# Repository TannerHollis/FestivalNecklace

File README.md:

# FestivalNecklace
 Fun RGB ATTiny Festival Necklace

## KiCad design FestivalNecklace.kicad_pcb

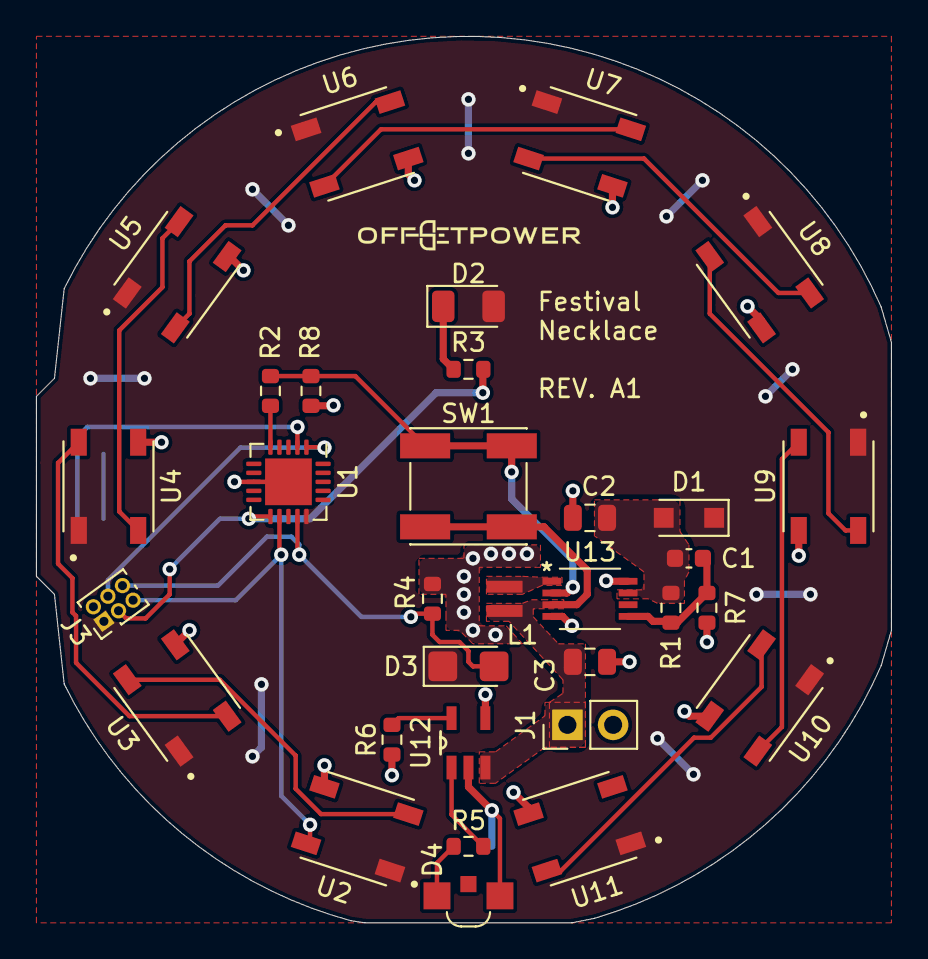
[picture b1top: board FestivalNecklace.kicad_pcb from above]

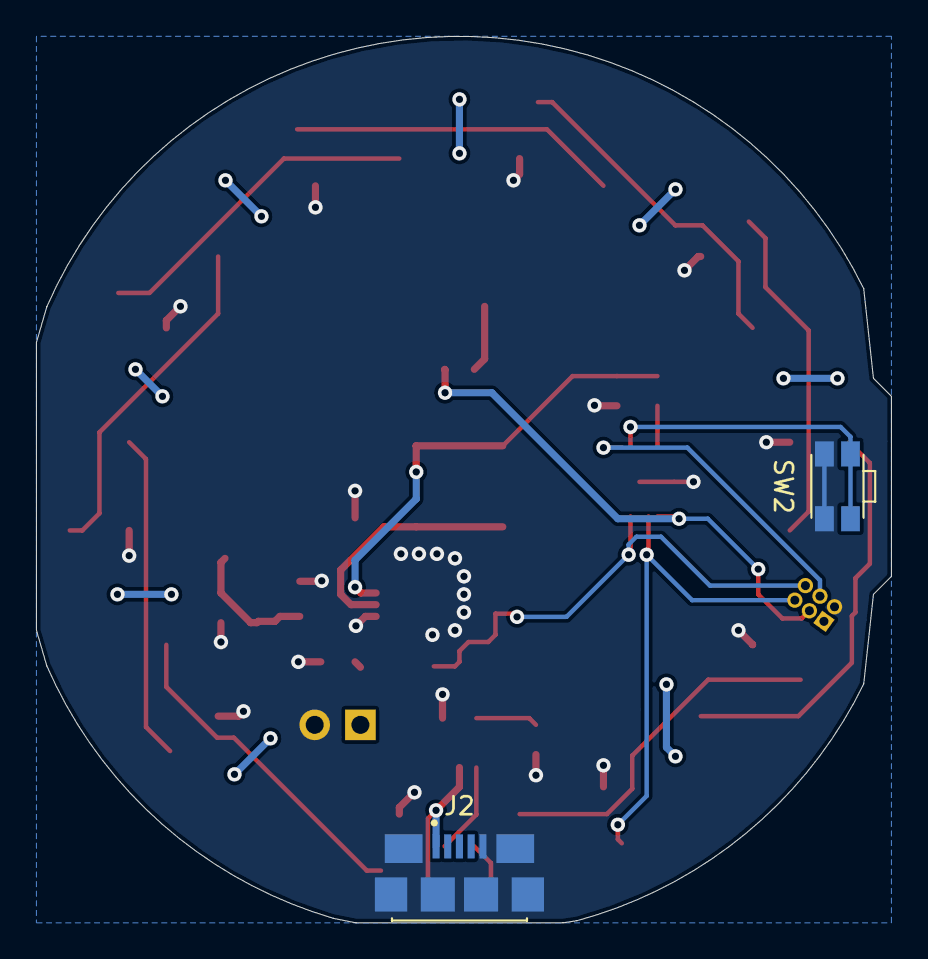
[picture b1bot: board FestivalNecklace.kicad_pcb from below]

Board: 2 copper layers, 47.5 x 49.2 mm, 34 parts (2 on the bottom side), 27 nets.

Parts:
C1: 1n; C_0603_1608Metric
C2: 22uF; C_0805_2012Metric
C3: 10uF; C_0805_2012Metric
D1: D_Schottky; D_SOD-123F
D2: LED; LED_1206_3216Metric
D3: D_Photo; LED_1206_3216Metric_Castellated
D4: LED; APA3010SECK
J1: Conn_01x02; PinHeader_1x02_P2.54mm_Vertical
J2: 10118192-0002LF; AMPHENOL_10118192-0002LF
J3: Conn_02x03_Odd_Even; PinHeader_2x03_P1.00mm_Vertical
L1: 2.2u; NRS2012T2R2MGJ
R1: 750k; R_0603_1608Metric
R2, R5: 1.5k; R_0603_1608Metric
R3: 50; R_0603_1608Metric
R4: 470k; R_0603_1608Metric
R6: 4.7k; R_0603_1608Metric
R7, R8: 100k; R_0603_1608Metric
SW1: SW_Push_Dual; TL3301NF260QG
SW2: SW_Push_Dual; EVQ-P7C01P
U1: ATtiny45V-10MU; QFN-20-1EP_4x4mm_P0.5mm_EP2.6x2.6mm
U2, U3, U4, U5, U6, U7, U8, U9, U10, U11: WS2812B-B; LED_WS2812B-B
U12: MCP73832T-2ACI_OT; SOT95P270X145-5N
U13: PAM2401SCADJ

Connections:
BTTN: SW2.2, U1.2
EN: R2.2, R8.2, SW1.1, U13.2
GND: C2.2, C3.2, J1.2, J2.5, J2.S1, J2.S2, J2.S3, J2.S4, J2.S5, J2.S6, J3.2, R4.1, R6.1, R7.1, R8.1, SW2.1, U1.8, U1.21, U2.3, U3.3, U4.3, U5.3, U6.3, U7.3, U8.3, U9.3, U10.3, U11.3, U12.4, U13.4, U13.8
IR_RX-CLK: D3.2, J3.6, R4.2, U1.14
IR_TX-MOSI: J3.3, R3.1, U1.11
LED_DO5: U6.2, U7.4
LED_DO-MISO: J3.5, U1.12, U2.4
unnamed: C1.1, C2.1, D1.2, R1.2, U13.7
unnamed: C1.2, R1.1, R7.2, U13.5
unnamed: D2.1, R3.2
unnamed: D4.1, R5.1
unnamed: D4.2, J2.1, U12.2
unnamed: L1.2, U13.1
unnamed: R5.2, U12.1
unnamed: R6.2, U12.5
unnamed: U2.2, U3.4
unnamed: U3.2, U4.4
unnamed: U4.2, U5.4
unnamed: U5.2, U6.4
unnamed: U7.2, U8.4
unnamed: U8.2, U9.4
unnamed: U10.2, U11.4
unnamed: U9.2, U10.4
PWR_EN: R2.1, U1.5
VBAT: C3.1, J1.1, L1.1, SW1.2, U12.3, U13.3
VCC: D1.1, D2.2, D3.1, J3.1, U1.15, U2.1, U3.1, U4.1, U5.1, U6.1, U7.1, U8.1, U9.1, U10.1, U11.1
~RESET~: J3.4, U1.1

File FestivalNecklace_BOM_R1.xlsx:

Item | Qty | Reference(s) | Value | LibPart | Footprint | DK_PN | MANUFACTURER | PARTNO | PREVIOUSLY ORDERD | AVAILABLE | PRICE | PRICE PER QUANTITY | QUANTITY NEEDED | DIGIKEY PARTNUMBER
1 | 1 | C1 | 1n | Device:C | Capacitor_SMD:C_0603_1608Metric | 1276-1018-1-ND | Samsung Electro-Mechanics | CL10B102KB8NNNC | Yes | 50 | 0.85 | 1.7000000000000001E-2
2 | 1 | C2 | 22uF | Device:C | Capacitor_SMD:C_0805_2012Metric | 1276-6460-1-ND | Samsung Electro-Mechanics | CL21A226MQQNNNG | Yes | 50 | 2.88 | 5.7599999999999998E-2
3 | 1 | C3 | 10uF | Device:C | Capacitor_SMD:C_0805_2012Metric | 1276-1298-1-ND | Samsung Electro-Mechanics | CL21A106MQFNNNE | Yes | 50 | 2.14 | 4.2800000000000005E-2
4 | 1 | D1 | D_Schottky | Device:D_Schottky | Diode_SMD:D_SOD-123F | 1727-5192-1-ND | Nexperia USA Inc. | PMEG2010ER | Yes | 50 | 15.95 | 0.31900000000000001
5 | 1 | D2 | LED | Device:LED | LED_SMD:LED_1206_3216Metric | 1080-1357-1-ND | Everlight Electronics Co Ltd | IR26-21C/L110/TR8 | Yes | 100 | 9.4700000000000006 | 9.4700000000000006E-2
6 | 1 | D3 | D_Photo | Device:D_Photo | LED_SMD:LED_1206_3216Metric_Castellated | 3147-B1501PD--H9B000113U1930CT-ND |  | B1501PD--H9B000113U1930 | Yes | 50 | 7 | 0.14000000000000001
7 | 1 | D4 | LED | Device:LED | FestivalNecklace:APA3010SECK | 754-1842-1-ND | Kingbright | APA3010SECK-GX | Yes | 50 | 14.35 | 0.28699999999999998
8 | 1 | J1 |  |  |  |  |  |  |  |  |  | 0
9 | 1 | J2 | 10118192-0002LF | FestivalNecklace:10118192-0002LF | FestivalNecklace:AMPHENOL_10118192-0002LF | 609-5379-1-ND | Amphenol ICC (FCI) | 10118192-0002LF | Yes | 25 | 8.83 | 0.35320000000000001
10 | 1 | J3 |  |  |  |  |  |  |  |  |  | 0
11 | 1 | L1 | 2.2u | Device:L | Inductor_SMD:L_0805_2012Metric | 1292-WLPH201610M2R2PPCT-ND | Walsin Technology Corporation | WLPH201610M2R2PP | Yes | 50 | 3.78 | 7.5600000000000001E-2
12 | 1 | R1 | 750k | Device:R | Resistor_SMD:R_0603_1608Metric | RMCF0603FT750KCT-ND | Stackpole Electronics Inc | RMCF0603FT750K | Yes | 100 | 0.68 | 6.8000000000000005E-3
13 | 2 | R2, R5 | 1.5k | Device:R | Resistor_SMD:R_0603_1608Metric | 311-1.50KHRCT-ND | YAGEO | RC0603FR-071K5L | Yes | 100 | 0.97 | 1.9400000000000001E-2
14 | 1 | R3 | 47 | Device:R | Resistor_SMD:R_0603_1608Metric | 10-ERJ-H3GJ470VCT-ND | Panasonic Electronic Components | ERJ-H3GJ470V | Yes | 100 | 5.38 | 5.3800000000000001E-2
15 | 1 | R4 | 470k | Device:R | Resistor_SMD:R_0603_1608Metric | A129720CT-ND | TE Connectivity Passive Product | CRGCQ0603F470K | Yes | 100 | 1.45 | 1.4499999999999999E-2
16 | 1 | R6 | 4.7k | Device:R | Resistor_SMD:R_0603_1608Metric | RR08P4.7KDCT-ND | Susumu | RR0816P-472-D | Yes | 100 | 3.42 | 3.4200000000000001E-2
17 | 2 | R7, R8 | 100k | Device:R | Resistor_SMD:R_0603_1608Metric | CR0603-JW-104ELFCT-ND | Bourns Inc. | CR0603-JW-104ELF | Yes | 100 | 0.36 | 7.1999999999999998E-3
18 | 1 | SW1 | SW_Push_Dual | Switch:SW_SPST | FestivalNecklace:TL3301NF260QG | EG4374CT-ND | E-Switch | TL3301AF160QJ | Yes | 50 | 21.54 | 0.43079999999999996
19 | 1 | SW2 | SW_Push_Dual | Switch:SW_SPST | FestivalNecklace:EVQ-P7C01P | P16765CT-ND | Panasonic Electronic Components | EVQ-P7C01P | Yes | 50 | 14.48 | 0.28960000000000002
20 | 1 | U1 | ATtiny45V-10MU | MCU_Microchip_ATtiny:ATtiny45V-10MU | Package_DFN_QFN:QFN-20-1EP_4x4mm_P0.5mm_EP2.6x2.6mm | ATTINY45V-10MU-ND | Microchip Technology | ATTINY45V-10MU | Yes | 25 | 44.85 | 1.794
21 | 10 | U2, U3, U4, U5, U6, U7, U8, U9, U10, U11 | WS2812B-B | FestivalNecklace:WS2812B-B | FestivalNecklace:LED_WS2812B-B |  | Worldsemi |  | Yes | 150 | 75 | 5
22 | 1 | U12 | MCP73832T-2ACI_OT | FestivalNecklace:MCP73832T-2ACI_OT | FestivalNecklace:SOT95P270X145-5N | MCP73832T-2ACI/OTCT-ND | Microchip Technology | MCP73832T-2ACI/OT | Yes | 25 | 15.75 | 0.63
23 | 1 | U13 | PAM2401SCADJ | FestivalNecklace:PAM2401SCADJ | FestivalNecklace:PAM2401SCADJ | PAM2401SCADJDICT-ND | Diodes Incorporated | PAM2401SCADJ | Yes | 25 | 22.26 | 0.89040000000000008
 |  |  |  |  |  |  |  | Subtotal |  |  | 271.39000000000004 | 10.557600000000001

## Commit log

2022-07-15 Commit
    WIP
2022-07-15 Changed a few thing...
    Not much tho.
